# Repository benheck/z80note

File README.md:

# z80note
Single board computer designed for Midwest Gaming Classic 2020 workshop

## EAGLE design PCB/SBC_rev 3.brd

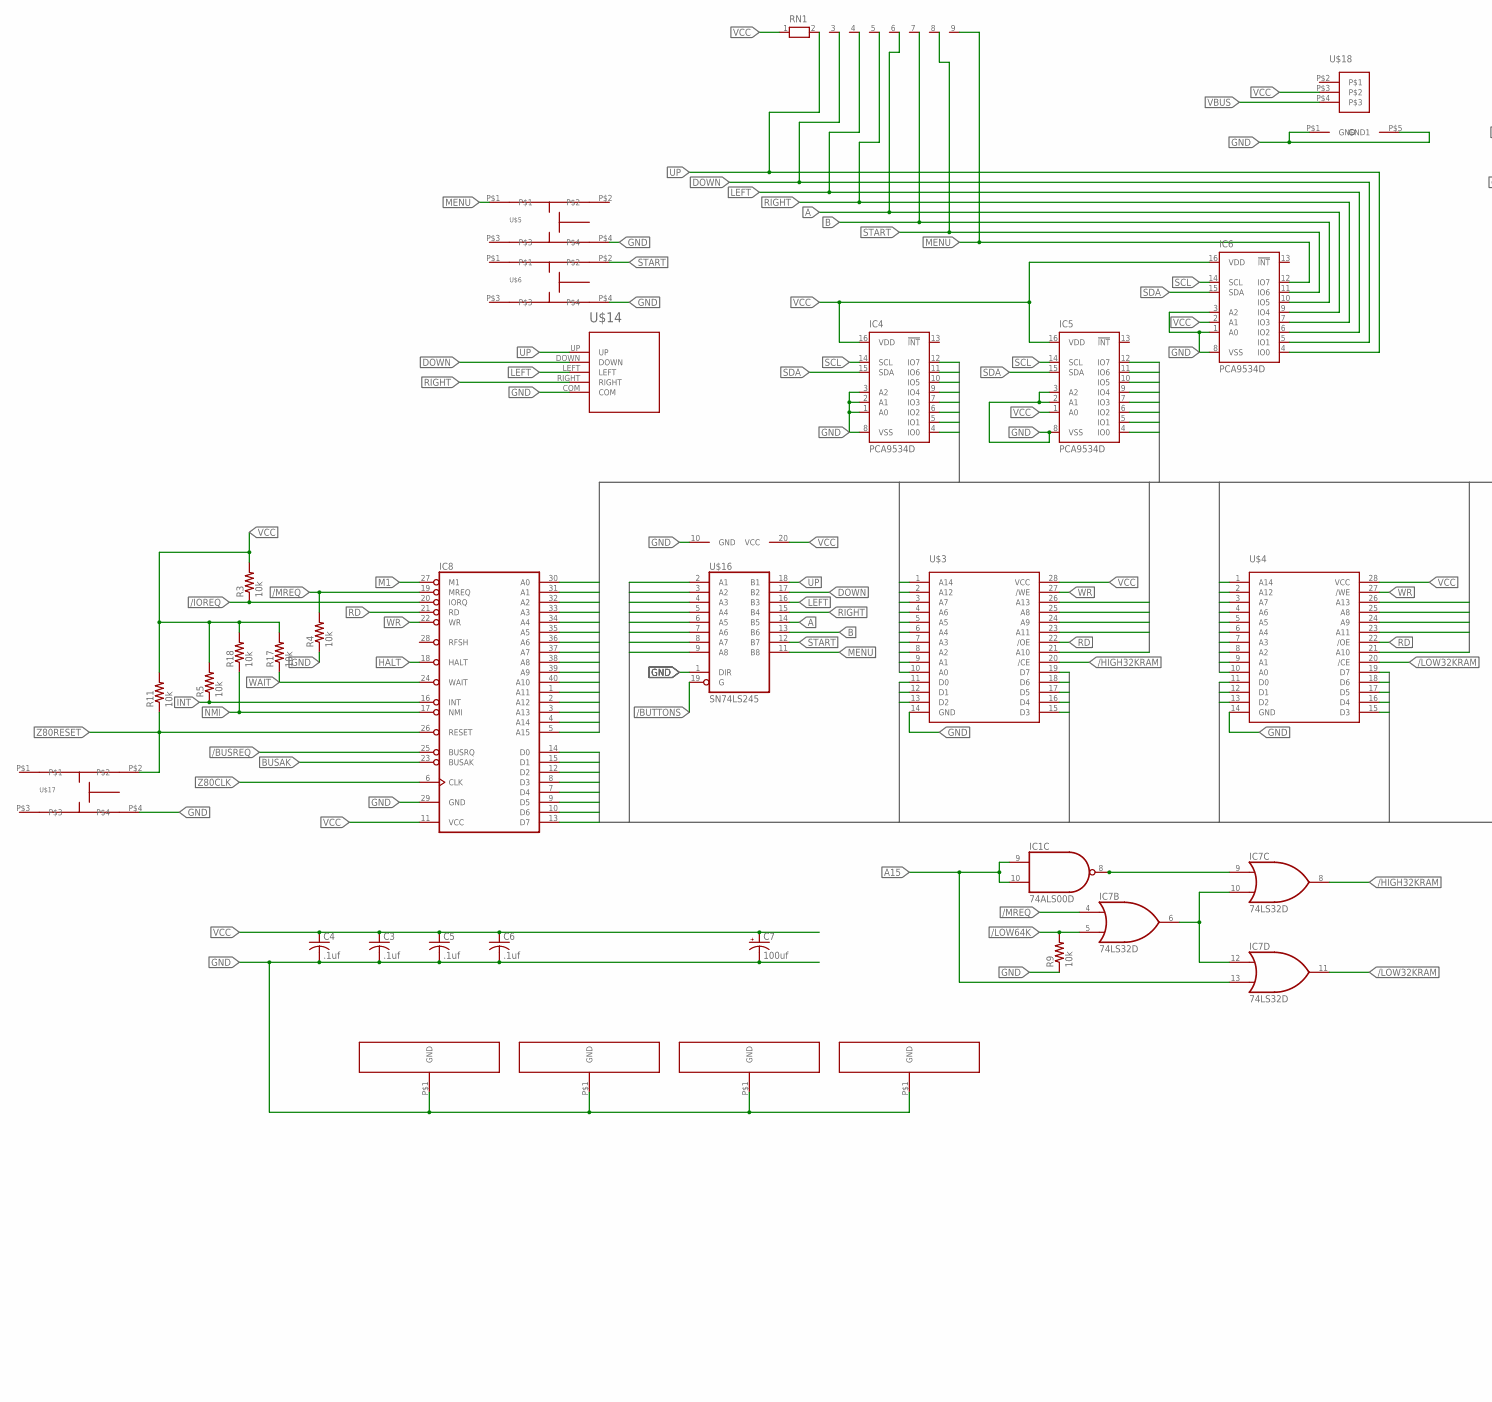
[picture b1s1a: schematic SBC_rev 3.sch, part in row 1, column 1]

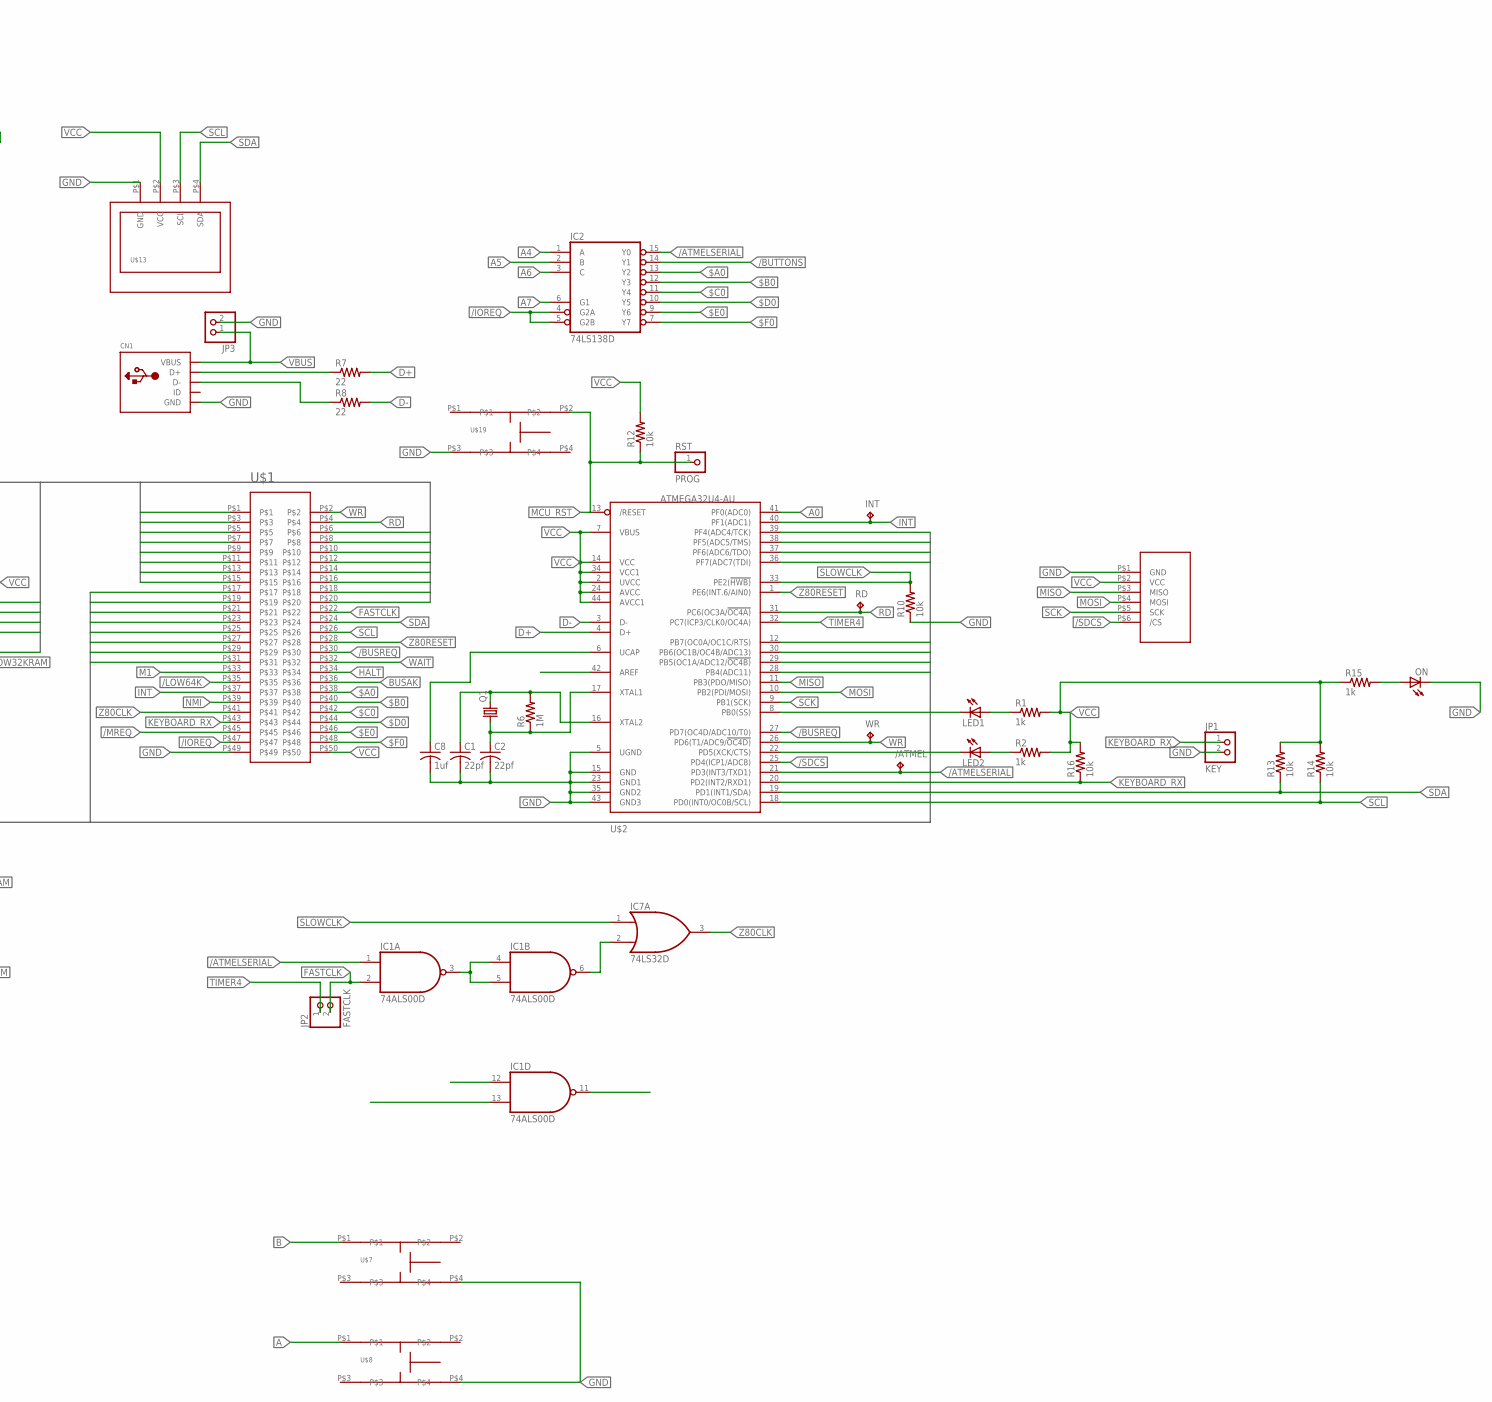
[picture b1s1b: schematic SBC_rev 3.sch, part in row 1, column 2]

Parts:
/ATMEL: TPB1,27; B1,27
C1, C2: 22pf; RESISTOR_C025-024X044
C3, C4, C5, C6: .1uf; RESISTOR_C025-024X044
C7: 100uf; E2,5-7
C8: 1uf; RESISTOR_C025-024X044
CN1: USBMOLEX; USB-MINIB-THM-MOLEX
IC1: 74ALS00D; SO14
IC2: 74LS138D; SO16
IC4, IC5, IC6: PCA9534D; SO16W
IC7: 74LS32D; SO14
IC8: Z80CPU; DIL40
INT: TPB1,27; B1,27
JP1: KEY; 1X02
JP2: FASTCLK; 1X02/90
JP3: PINHD-1X2/90; 1X02/90
LED1, LED2: LED3MM
ON: LED3MM
Q1: CRYSTALHC49S; HC49/S
R1, R2, R15: 1k; R1206
R3, R4, R5, R9, R10, R11, R12, R13, R14, R16, R17, R18: 10k; R1206
R6: 1M; R1206
R7, R8: 22; R1206
RD: TPB1,27; B1,27
RN1: RN08; RN-9
RST: PROG; 1X01
SD_ADAPTER: SD_ADAPTER; SD_RIGHTANGLE
U$1: CARDSLOT50; CARD50
U$2: ATMEGA32U4-AU; TQFP44
U$3, U$4: IS65C256AL_32KRAM; SO28-3
U$5, U$6, U$7, U$8, U$17, U$19: TACT; 6MM_TACT
U$9, U$10, U$11, U$12: GND_STRIP; GND_PADS
U$13: OLED_SSD1306_I2C; OLED_128X64_I2C
U$14: SKQUCAA010
U$16: SN74LS245; SO20L
U$18: SWITCH_1825232-1; SWITCH
WR: TPB1,27; B1,27

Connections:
$A0: IC2.13 (Y2), U$1.P$38
$B0: IC2.12 (Y3), U$1.P$40
$C0: IC2.11 (Y4), U$1.P$42
$D0: IC2.10 (Y5), U$1.P$44
$E0: IC2.9 (Y6), U$1.P$46
$F0: IC2.7 (Y7), U$1.P$48
/ATMELSERIAL: /ATMEL.TP, IC1.1 (I0), IC2.15 (Y0), U$2.21 (PD3(INT3/TXD1))
/BUSREQ: IC8.25 (BUSRQ), U$1.P$30, U$2.27 (PD7(OC4D/ADC10/T0))
/BUTTONS: IC2.14 (Y1), U$16.19 (G)
/HIGH32KRAM: IC7.8 (O), U$3.20 (/CE)
/IOREQ: IC2.4 (G2A), IC2.5 (G2B), IC8.20 (IORQ), R3.1, U$1.P$47
/LOW32KRAM: IC7.11 (O), U$4.20 (/CE)
/LOW64K: IC7.5 (I1), R9.2, U$1.P$35
/MREQ: IC7.4 (I0), IC8.19 (MREQ), R4.2, U$1.P$45
/SDCS: SD_ADAPTER.P$6 (/CS), U$2.25 (PD4(ICP1/ADC8))
A: IC6.9 (IO4), RN1.6, U$8.P$1, U$16.14 (B5)
A0: IC4.4 (IO0), IC8.30 (A0), U$1.P$15, U$2.41 (PF0(ADC0)), U$3.10 (A0), U$4.10 (A0)
A1: IC4.5 (IO1), IC8.31 (A1), U$1.P$13, U$3.9 (A1), U$4.9 (A1)
A2: IC4.6 (IO2), IC8.32 (A2), U$1.P$11, U$3.8 (A2), U$4.8 (A2)
A3: IC4.7 (IO3), IC8.33 (A3), U$1.P$9, U$3.7 (A3), U$4.7 (A3)
A4: IC2.1 (A), IC4.9 (IO4), IC8.34 (A4), U$1.P$7, U$3.6 (A4), U$4.6 (A4)
A5: IC2.2 (B), IC4.10 (IO5), IC8.35 (A5), U$1.P$5, U$3.5 (A5), U$4.5 (A5)
A6: IC2.3 (C), IC4.11 (IO6), IC8.36 (A6), U$1.P$3, U$3.4 (A6), U$4.4 (A6)
A7: IC2.6 (G1), IC4.12 (IO7), IC8.37 (A7), U$1.P$1, U$3.3 (A7), U$4.3 (A7)
A8: IC5.4 (IO0), IC8.38 (A8), U$1.P$6, U$3.25 (A8), U$4.25 (A8)
A9: IC5.5 (IO1), IC8.39 (A9), U$1.P$8, U$3.24 (A9), U$4.24 (A9)
A10: IC5.6 (IO2), IC8.40 (A10), U$1.P$10, U$3.21 (A10), U$4.21 (A10)
A11: IC5.7 (IO3), IC8.1 (A11), U$1.P$12, U$3.23 (A11), U$4.23 (A11)
A12: IC5.9 (IO4), IC8.2 (A12), U$1.P$14, U$3.2 (A12), U$4.2 (A12)
A13: IC5.10 (IO5), IC8.3 (A13), U$1.P$16, U$3.26 (A13), U$4.26 (A13)
A14: IC5.11 (IO6), IC8.4 (A14), U$1.P$18, U$3.1 (A14), U$4.1 (A14)
A15: IC1.9 (I0), IC1.10 (I1), IC5.12 (IO7), IC7.13 (I1), IC8.5 (A15), U$1.P$20
AREF: U$2.42 (AREF)
B: IC6.10 (IO5), RN1.7, U$7.P$1, U$16.13 (B6)
BUSAK: IC8.23 (BUSAK), U$1.P$36
D0: IC8.14 (D0), U$1.P$17, U$2.39 (PF4(ADC4/TCK)), U$3.11 (D0), U$4.11 (D0), U$16.2 (A1)
D1: IC8.15 (D1), U$1.P$19, U$2.38 (PF5(ADC5/TMS)), U$3.12 (D1), U$4.12 (D1), U$16.3 (A2)
D2: IC8.12 (D2), U$1.P$21, U$2.37 (PF6(ADC6/TDO)), U$3.13 (D2), U$4.13 (D2), U$16.4 (A3)
D3: IC8.8 (D3), U$1.P$23, U$2.36 (PF7(ADC7(TDI)), U$3.15 (D3), U$4.15 (D3), U$16.5 (A4)
D4: IC8.7 (D4), U$1.P$25, U$2.28 (PB4(ADC11)), U$3.16 (D4), U$4.16 (D4), U$16.6 (A5)
D5: IC8.9 (D5), U$1.P$27, U$2.29 (PB5(OC1A/ADC12/!OC4B)), U$3.17 (D5), U$4.17 (D5), U$16.7 (A6)
D6: IC8.10 (D6), U$1.P$29, U$2.30 (PB6(OC1B/OC4B/ADC13)), U$3.18 (D6), U$4.18 (D6), U$16.8 (A7)
D7: IC8.13 (D7), U$1.P$31, U$2.12 (PB7(OC0A/OC1C/RTS)), U$3.19 (D7), U$4.19 (D7), U$16.9 (A8)
D+: R7.2, U$2.4 (D+)
D-: R8.2, U$2.3 (D-)
DOWN: IC6.5 (IO1), RN1.3, U$14.DOWN, U$16.17 (B2)
FASTCLK: IC1.2 (I1), JP2.2, U$1.P$22
GND: C1.2, C2.2, C3.2, C4.2, C5.2, C6.2, C7.-, C8.2, CN1.GND, IC1.7 (GND), IC2.8 (GND), IC4.1 (A0), IC4.2 (A1), IC4.3 (A2), IC4.8 (VSS), IC5.2 (A1), IC5.3 (A2), IC5.8 (VSS), IC6.1 (A0), IC6.3 (A2), IC6.8 (VSS), IC7.7 (GND), IC8.29 (GND), JP1.2, JP3.2, ON.K (C), R4.1, R9.1, R10.1, SD_ADAPTER.P$1 (GND), U$1.P$49, U$2.5 (UGND), U$2.15 (GND), U$2.23 (GND1), U$2.35 (GND2), U$2.43 (GND3), U$3.14 (GND), U$4.14 (GND), U$5.P$4, U$6.P$4, U$7.P$4, U$8.P$4, U$9.P$1, U$10.P$1, U$11.P$1, U$12.P$1, U$13.P$1 (GND), U$14.COM, U$16.1 (DIR), U$16.10 (GND), U$17.P$4, U$18.P$1 (GND), U$18.P$5 (GND1), U$19.P$3
HALT: IC8.18 (HALT), U$1.P$34
INT: IC8.16 (INT), INT.TP, R5.1, U$1.P$37, U$2.40 (PF1(ADC1))
KEYBOARD_RX: JP1.1, R16.1, U$1.P$43, U$2.20 (PD2(INT2/RXD1))
LED1: LED1.K (C), U$2.8 (PB0(SS))
LED2: LED2.K (C), U$2.22 (PD5(XCK/CTS))
LEFT: IC6.6 (IO2), RN1.4, U$14.LEFT, U$16.16 (B3)
M1: IC8.27 (M1), U$1.P$33
MCU_RST: R12.1, RST.1, U$2.13 (/RESET), U$19.P$2
MENU: IC6.12 (IO7), RN1.9, U$5.P$1, U$16.11 (B8)
MISO: SD_ADAPTER.P$3 (MISO), U$2.11 (PB3(PDO/MISO))
MOSI: SD_ADAPTER.P$4 (MOSI), U$2.10 (PB2(PDI/MOSI))
unnamed: C1.1, Q1.2, R6.2, U$2.16 (XTAL2)
unnamed: C2.1, Q1.1, R6.1, U$2.17 (XTAL1)
unnamed: ON.A, R15.2
unnamed: IC1.3 (O), IC1.4 (I0), IC1.5 (I1)
unnamed: LED1.A, R1.1
unnamed: IC1.6 (O), IC7.2 (I1)
unnamed: IC7.6 (O), IC7.10 (I1), IC7.12 (I0)
unnamed: LED2.A, R2.1
unnamed: IC1.8 (O), IC7.9 (I0)
unnamed: CN1.D+, R7.1
unnamed: CN1.D-, R8.1
NMI: IC8.17 (NMI), R18.1, U$1.P$39
RD: IC8.21 (RD), RD.TP, U$1.P$4, U$2.31 (PC6(OC3A/!OC4A)), U$3.22 (/OE), U$4.22 (/OE)
RIGHT: IC6.7 (IO3), RN1.5, U$14.RIGHT, U$16.15 (B4)
SCK: SD_ADAPTER.P$5 (SCK), U$2.9 (PB1(SCK))
SCL: IC4.14 (SCL), IC5.14 (SCL), IC6.14 (SCL), R14.1, U$1.P$26, U$2.18 (PD0(INT0/OC0B/SCL)), U$13.P$3 (SCL)
SDA: IC4.15 (SDA), IC5.15 (SDA), IC6.15 (SDA), R13.1, U$1.P$24, U$2.19 (PD1(INT1/SDA)), U$13.P$4 (SDA)
SLOWCLK: IC7.1 (I0), R10.2, U$2.33 (PE2(!HWB))
START: IC6.11 (IO6), RN1.8, U$6.P$2, U$16.12 (B7)
TIMER4: JP2.1, U$2.32 (PC7(ICP3/CLK0/OC4A))
UCAP: C8.1, U$2.6 (UCAP)
UP: IC6.4 (IO0), RN1.2, U$14.UP, U$16.18 (B1)
VBUS: CN1.VBUS, JP3.1, U$18.P$4
VCC: C3.1, C4.1, C5.1, C6.1, C7.+, IC1.14 (VCC), IC2.16 (VCC), IC4.16 (VDD), IC5.1 (A0), IC5.16 (VDD), IC6.2 (A1), IC6.16 (VDD), IC7.14 (VCC), IC8.11 (VCC), R1.2, R2.2, R3.2, R5.2, R11.2, R12.2, R13.2, R14.2, R15.1, R16.2, R17.2, R18.2, RN1.1, SD_ADAPTER.P$2 (VCC), U$1.P$50, U$2.2 (UVCC), U$2.7 (VBUS), U$2.14 (VCC), U$2.24 (AVCC), U$2.34 (VCC1), U$2.44 (AVCC1), U$3.28 (VCC), U$4.28 (VCC), U$13.P$2 (VCC), U$16.20 (VCC), U$18.P$3
WAIT: IC8.24 (WAIT), R17.1, U$1.P$32
WR: IC8.22 (WR), U$1.P$2, U$2.26 (PD6(T1/ADC9/!OC4D)), U$3.27 (/WE), U$4.27 (/WE), WR.TP
Z80CLK: IC7.3 (O), IC8.6 (CLK), U$1.P$41
Z80RESET: IC8.26 (RESET), R11.1, U$1.P$28, U$2.1 (PE6(INT.6/AIN0)), U$17.P$2

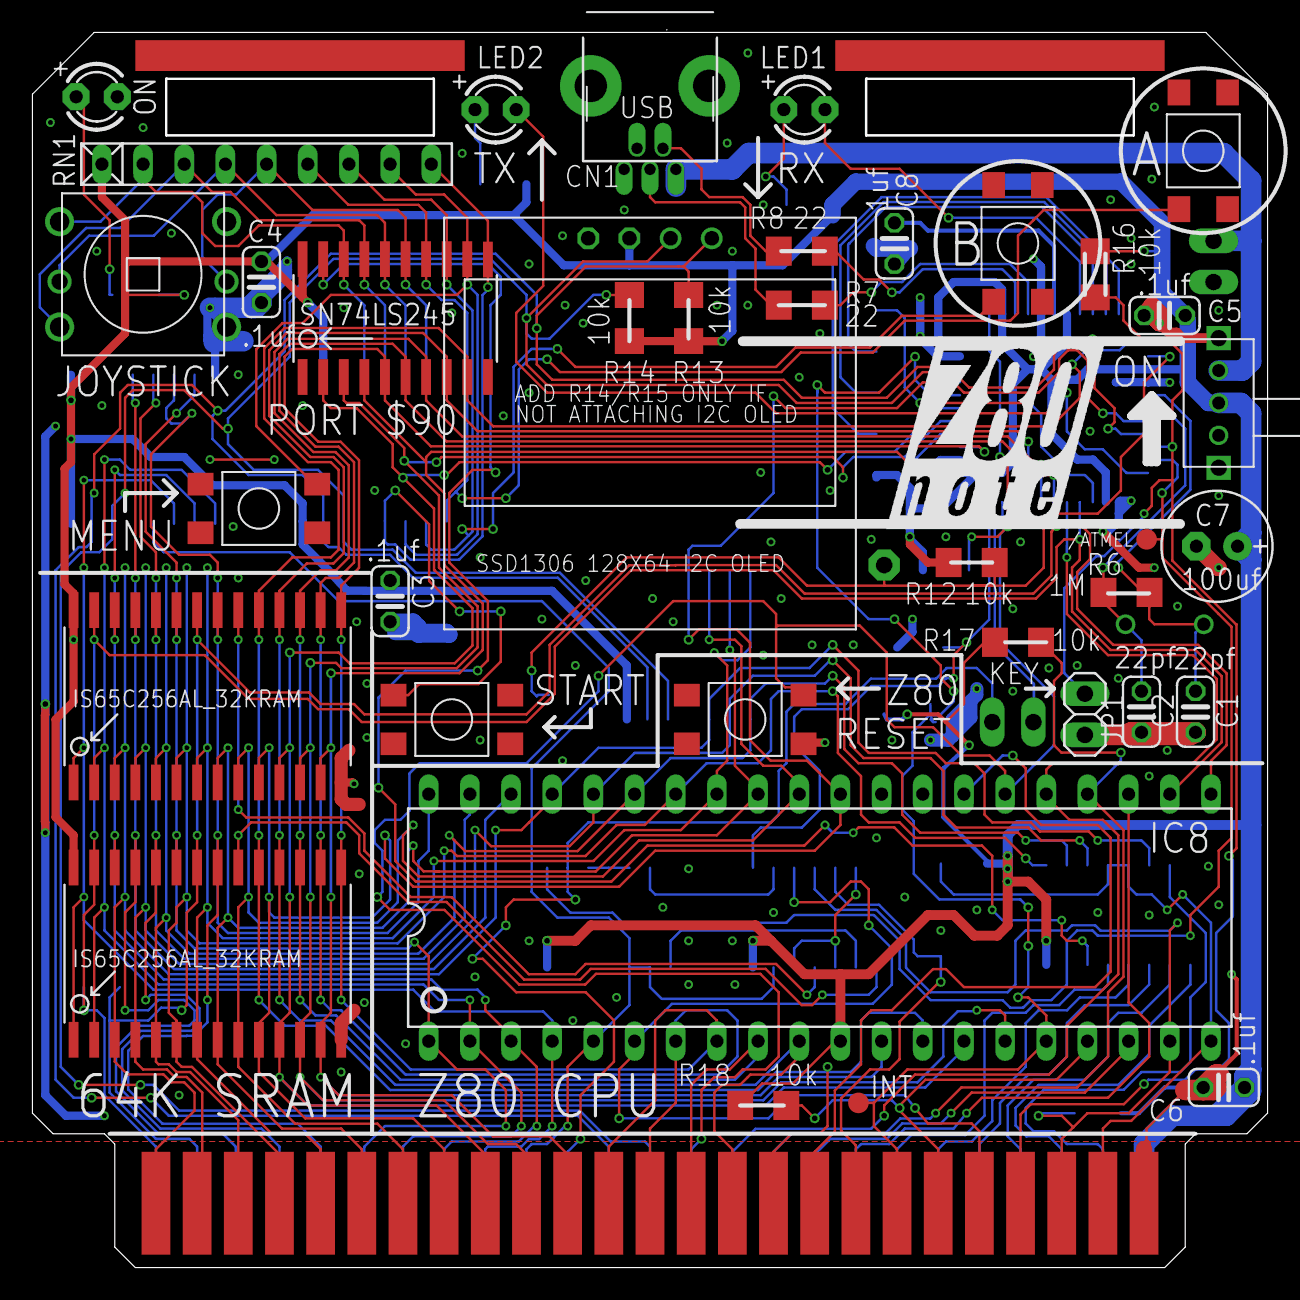
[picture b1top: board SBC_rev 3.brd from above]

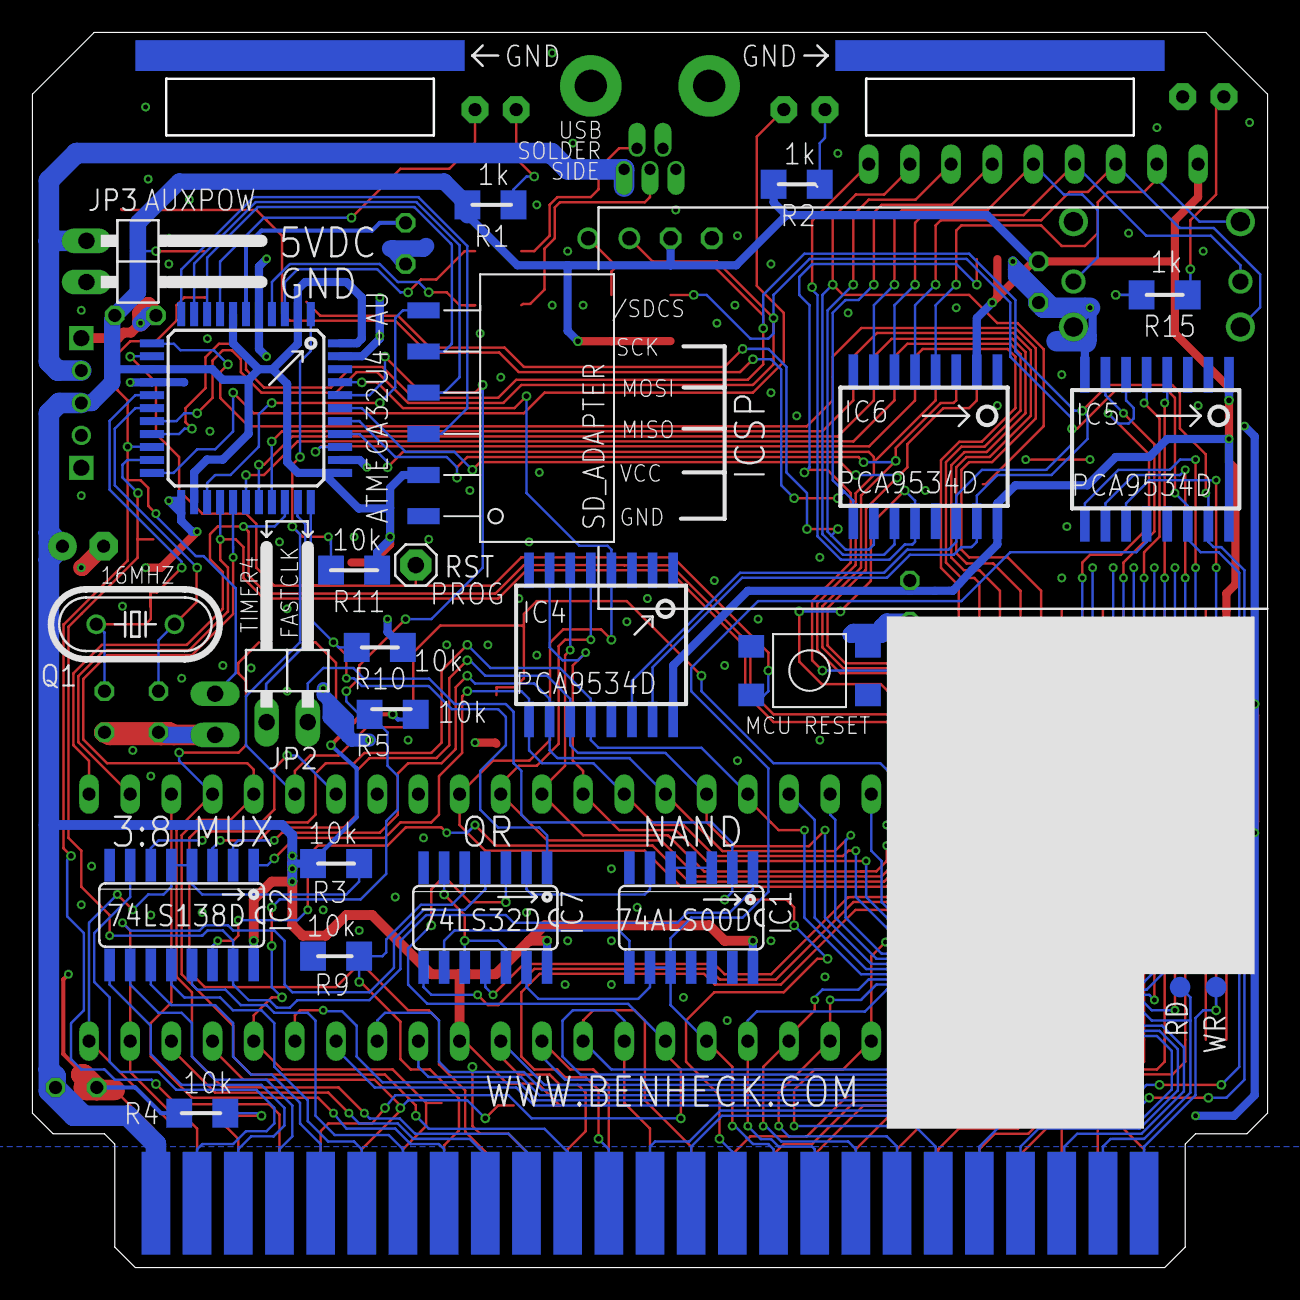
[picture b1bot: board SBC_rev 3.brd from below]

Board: 2 copper layers, 76.0 x 76.0 mm, 67 parts (26 on the bottom side), 86 nets.

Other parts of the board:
U$15: Z80LOGO

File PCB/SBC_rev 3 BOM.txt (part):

Partlist exported from //benheck-server/Projects/2020/MGC Z80 Project/PCB designs DIP40/SBC_rev 3.sch at 3/7/2020 6:08 PM

Part       Value             Device                   Package               Description                                               MF MPN       OC_FARNELL OC_NEWARK SPICEPREFIX TP_SIGNAL_NAME
/ATMEL     TPB1,27           TPB1,27                  B1,27                 Test pad                                                                                                              
C1         22pf              RESISTOR_C-US025-024X044 RESISTOR_C025-024X044 CAPACITOR, American symbol                                                                                            
C2         22pf              RESISTOR_C-US025-024X044 RESISTOR_C025-024X044 CAPACITOR, American symbol                                                                                            
C3         .1uf              RESISTOR_C-US025-024X044 RESISTOR_C025-024X044 CAPACITOR, American symbol                                                                                            
C4         .1uf              RESISTOR_C-US025-024X044 RESISTOR_C025-024X044 CAPACITOR, American symbol                                                                                            
C5         .1uf              RESISTOR_C-US025-024X044 RESISTOR_C025-024X044 CAPACITOR, American symbol                                                                                            
C6         .1uf              RESISTOR_C-US025-024X044 RESISTOR_C025-024X044 CAPACITOR, American symbol                                                                                            
C7         100uf             CPOL-USE2.5-7            E2,5-7                POLARIZED CAPACITOR, American symbol                                                                                  
C8         1uf               RESISTOR_C-US025-024X044 RESISTOR_C025-024X044 CAPACITOR, American symbol                                                                                            
CN1                          USBMOLEX                 USB-MINIB-THM-MOLEX   USB Connectors                                                                                                        
IC1        74ALS00D          74ALS00D                 SO14                  Quad 2-input NAND gate                                                                                                
IC2        74LS138D          74LS138D                 SO16                  3-line to 8-line DECODER/DEMULTIPLEXER                                                                                
IC4        PCA9534D          PCA9534D                 SO16W                 8-bit I2C-bus and SMBus low power I/O port with interrupt    PCA9534DB 1408284    18M7513                             
IC5        PCA9534D          PCA9534D                 SO16W                 8-bit I2C-bus and SMBus low power I/O port with interrupt    PCA9534DB 1408284    18M7513                             
IC6        PCA9534D          PCA9534D                 SO16W                 8-bit I2C-bus and SMBus low power I/O port with interrupt    PCA9534DB 1408284    18M7513                             
IC7        74LS32D           74LS32D                  SO14                  Quad 2-input OR gate                                                                                                  
IC8                          Z80CPU                   DIL40                 Z80 FAMILY DEVICE                                                                                                     
INT        TPB1,27           TPB1,27                  B1,27                 Test pad                                                                                                              
JP1        KEY               PINHD-1X2                1X02                  PIN HEADER                                                                                                            
JP2        FASTCLK           PINHD-1X2/90             1X02/90               PIN HEADER                                                                                                            
JP3                          PINHD-1X2/90             1X02/90               PIN HEADER                                                                                                            
LED1                         LED3MM                   LED3MM                LED                                                                                                                   
LED2                         LED3MM                   LED3MM                LED                                                                                                                   
ON                           LED3MM                   LED3MM                LED                                                                                                                   
Q1                           CRYSTALHC49S             HC49/S                CRYSTAL                                                                1667008    unknown                             
R1         1k                R-US_R1206               R1206                 RESISTOR, American symbol                                                                   R                         
R2         1k                R-US_R1206               R1206                 RESISTOR, American symbol                                                                   R                         
R3         10k               R-US_R1206               R1206                 RESISTOR, American symbol                                                                   R                         
R4         10k               R-US_R1206               R1206                 RESISTOR, American symbol                                                                   R                         
R5         10k               R-US_R1206               R1206                 RESISTOR, American symbol                                                                   R                         
R6         1M                R-US_R1206               R1206                 RESISTOR, American symbol                                                                   R                         
R7         22                R-US_R1206               R1206                 RESISTOR, American symbol                                                                   R                         
R8         22                R-US_R1206               R1206                 RESISTOR, American symbol                                                                   R                         
R9         10k               R-US_R1206               R1206                 RESISTOR, American symbol                                                                   R                         
R10        10k               R-US_R1206               R1206                 RESISTOR, American symbol                                                                   R                         
R11        10k               R-US_R1206               R1206                 RESISTOR, American symbol                                                                   R                         
R12        10k               R-US_R1206               R1206                 RESISTOR, American symbol                                                                   R                         
R13        10k               R-US_R1206               R1206                 RESISTOR, American symbol                                                                   R                         
R14        10k               R-US_R1206               R1206                 RESISTOR, American symbol                                                                   R                         
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
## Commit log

2020-02-17 Added files
2020-02-17 Added image of schematic
2020-03-08 Updated file structure
2020-03-09 More updates
2020-03-09 Version sent to OSHpark
2020-03-16 Ch-ch-ch-ch-changes
2020-08-16 New graphics modes
2020-08-30 Pre-vacation updates
2020-10-02 Added BOM
2020-10-12 Memory tweaks
2020-10-18 Reduced memory footprint
2021-05-20 Added custom INIT files (with changes for MCU serial)
